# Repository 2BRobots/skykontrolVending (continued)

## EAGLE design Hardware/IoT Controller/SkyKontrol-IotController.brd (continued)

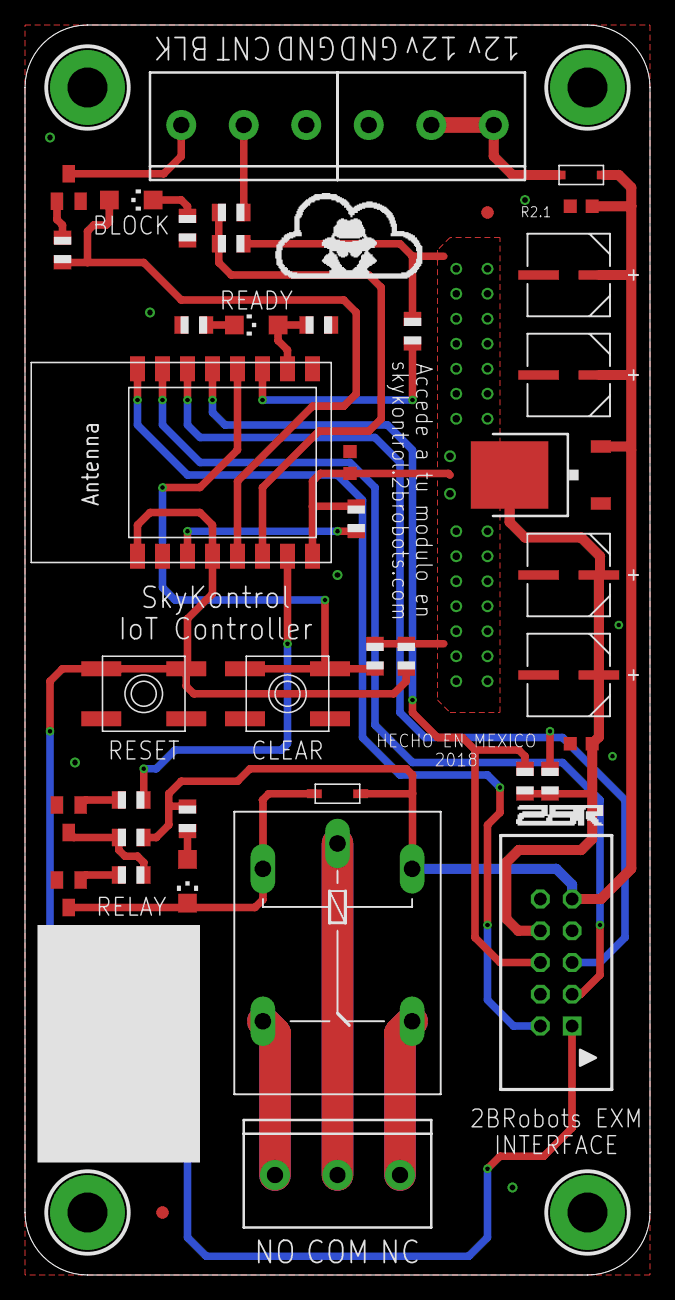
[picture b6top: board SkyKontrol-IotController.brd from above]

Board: 2 copper layers, 50.0 x 100.0 mm, 42 parts (0 on the bottom side), 29 nets.

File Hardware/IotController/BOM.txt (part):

Part Value           Device                    Package             Description                                                                                                     MF MPN           OC_FARNELL OC_NEWARK PACKAGE POPULARITY PROD_ID    SF_SKU    SUPPLIER  TOLERANCE VALUE VOLTAGERATING
C1   100UF           EEE-HA1E101XP-CASE-D8     CAPAE660X800N       Aluminum Electrolytic Capacitors,Surface Mount Type                                                                EEE-HA1E101XP 1973328    58T9236   CASE-D8                                 PANASONIC ±20 %     100UF 25V          
C2   100UF           EEE-HA1E101XP-CASE-D8     CAPAE660X800N       Aluminum Electrolytic Capacitors,Surface Mount Type                                                                EEE-HA1E101XP 1973328    58T9236   CASE-D8                                 PANASONIC ±20 %     100UF 25V          
C3   0.1uF           C-USC0603K                C0603K              CAPACITOR, American symbol                                                                                                                                                                                                           
C4   100UF           EEE-HA1E101XP-CASE-D8     CAPAE660X800N       Aluminum Electrolytic Capacitors,Surface Mount Type                                                                EEE-HA1E101XP 1973328    58T9236   CASE-D8                                 PANASONIC ±20 %     100UF 25V          
C5   100UF           EEE-HA1E101XP-CASE-D8     CAPAE660X800N       Aluminum Electrolytic Capacitors,Surface Mount Type                                                                EEE-HA1E101XP 1973328    58T9236   CASE-D8                                 PANASONIC ±20 %     100UF 25V          
C6   0.1uF           C-USC0603K                C0603K              CAPACITOR, American symbol                                                                                                                                                                                                           
C7   0.1uF           C-USC0603K                C0603K              CAPACITOR, American symbol                                                                                                                                                                                                           
D1   1N5819HW        DIODESOD-123              SOD-123             Diode                                                                                                                                                                                                                                
D2   MMSD301T        DIODESOD-123              SOD-123             Diode                                                                                                                                                                                                                                
IC1  NCP1117DT33G    LM1117TO252               TO252                                                                                                                                                                                                                                                    
J1                   CONN_03-SCREW-5MM         SCREWTERMINAL-5MM-3 Multi connection point. Often used as Generic Header-pin footprint for 0.1 inch spaced/style header connections                                                          CONN-10134 PRT-08433                                        
J2                   CONN_03-SCREW-5MM         SCREWTERMINAL-5MM-3 Multi connection point. Often used as Generic Header-pin footprint for 0.1 inch spaced/style header connections                                                          CONN-10134 PRT-08433                                        
J3                   CONN_03-SCREW-5MM         SCREWTERMINAL-5MM-3 Multi connection point. Often used as Generic Header-pin footprint for 0.1 inch spaced/style header connections                                                          CONN-10134 PRT-08433                                        
J4   SBH11-PBPC-D05  SBH11-PBPC-D05            SBH11-PBPC-D05      HEADER - Vertical, Shrouded                                                                                                                                                                                                          
K1   G5LE            G5LE                      G5LE                RELAY                                                                                                                            unknown    unknown           13                                                                     
LED1 Red             LEDCHIPLED_1206           CHIPLED_1206        LED                                                                                                                                                                                                                                  
LED2 Green           LEDCHIPLED_1206           CHIPLED_1206        LED                                                                                                                                                                                                                                  
LED3 Yellow          LEDCHIPLED_1206           CHIPLED_1206        LED                                                                                                                                                                                                                                  
R1   2k2             R-US_R0805                R0805               RESISTOR, American symbol                                                                                                                                                                                                            
R2   1k              R-US_R0805                R0805               RESISTOR, American symbol                                                                                                                                                                                                            
R3   10k             R-US_R0805                R0805               RESISTOR, American symbol                                                                                                                                                                                                            
R4   1k              R-US_R0805                R0805               RESISTOR, American symbol                                                                                                                                                                                                            
R5   10k             R-US_R0805                R0805               RESISTOR, American symbol                                                                                                                                                                                                            
R6   1k              R-US_R0805                R0805               RESISTOR, American symbol                                                                                                                                                                                                            
R7   2k2             R-US_R0805                R0805               RESISTOR, American symbol                                                                                                                                                                                                            
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
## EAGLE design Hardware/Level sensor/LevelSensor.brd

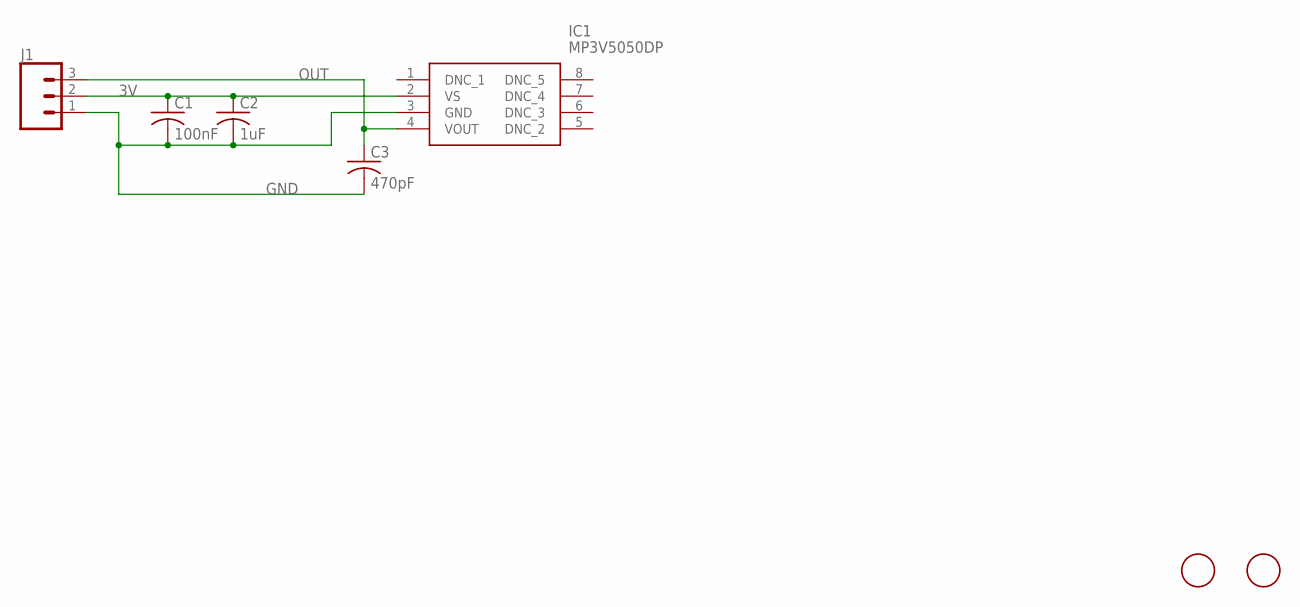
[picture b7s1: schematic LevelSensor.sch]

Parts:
C1: 100nF; C0603K
C2: 1uF; C0603K
C3: 470pF; C0805K
IC1: MP3V5050DP; SOP254P1753X991-8N
J1: CONN_03-SCREW-5MM; SCREWTERMINAL-5MM-3
U$2, U$3: FIDUCIAL; FIDUCIAL_1MM

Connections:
3V: C1.1, C2.1, IC1.2 (VS), J1.2
GND: C1.2, C2.2, C3.2, IC1.3 (GND), J1.1
OUT: C3.1, IC1.4 (VOUT), J1.3

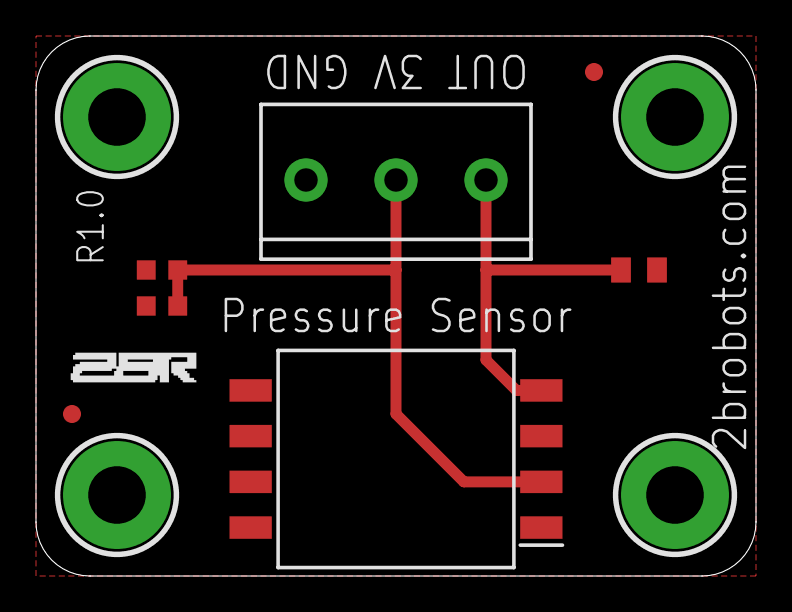
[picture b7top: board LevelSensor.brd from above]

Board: 2 copper layers, 40.0 x 30.0 mm, 7 parts (0 on the bottom side), 3 nets.

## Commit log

2019-12-06 Update LICENSE
2019-12-06 Licensed as CC-BY-NC-SA
2019-12-06 pcb design files
2019-12-24 new modules
2019-12-30 documentation add
2020-01-12 close
2020-01-13 lcd firmware
2020-01-23 web app
2020-01-23 security fail
2020-02-05 changed to P12F1840
    Changed the microcontroller for the PIC 12F1840 instead of the 12F1822 and release of the first functional firmware.
2020-02-11 powerMeter
2020-02-13 BOM and corrections
2020-02-14 pre-release
2020-02-21 slot expansion
2020-02-22 bugfix
2020-02-26 release
2021-02-02 project updates
2021-02-02 pcb corrected
2021-02-03 Watchdog module add
2021-02-21 LED polarity marks fix
2021-09-09 Update project
